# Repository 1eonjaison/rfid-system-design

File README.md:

# RFID System Design

This project is a custom PCB designed for a potential RFID-based key fob system.

The PCB incorporates a planar spiral coil, electronic components, switches and connections for a display. The project focuses on applying electronic circuit design and PCB layout principles.

---

## How It Works

The system is designed around a PCB spiral coil that may be used for inductive communication with RFID tags or key fobs.

The PCB design includes:

- **Spiral Coil** – A PCB-integrated coil intended for inductive signal transmission or reception.
- **Electronic Circuitry** – Components and connections for processing electrical signals.
- **Battery Holder** – Provides a connection for a coin-cell battery.
- **Switches** – Allow user interaction with the circuit.
- **Display Connections** – A footprint for connecting an LCD display.
- **Test Points** – Allow electrical measurements and circuit testing.

---

## PCB Design

The project involved:

- Designing the PCB layout.
- Placing electronic components and footprints.
- Routing electrical connections between components.
- Creating a planar spiral coil.
- Using copper layers and ground regions.
- Producing a physical PCB prototype.

---

## Project Evaluation

This project helped me develop my understanding of PCB design, component placement, circuit routing and electronic system development.

It also provided practical experience in translating a digital PCB layout into a manufactured circuit board.

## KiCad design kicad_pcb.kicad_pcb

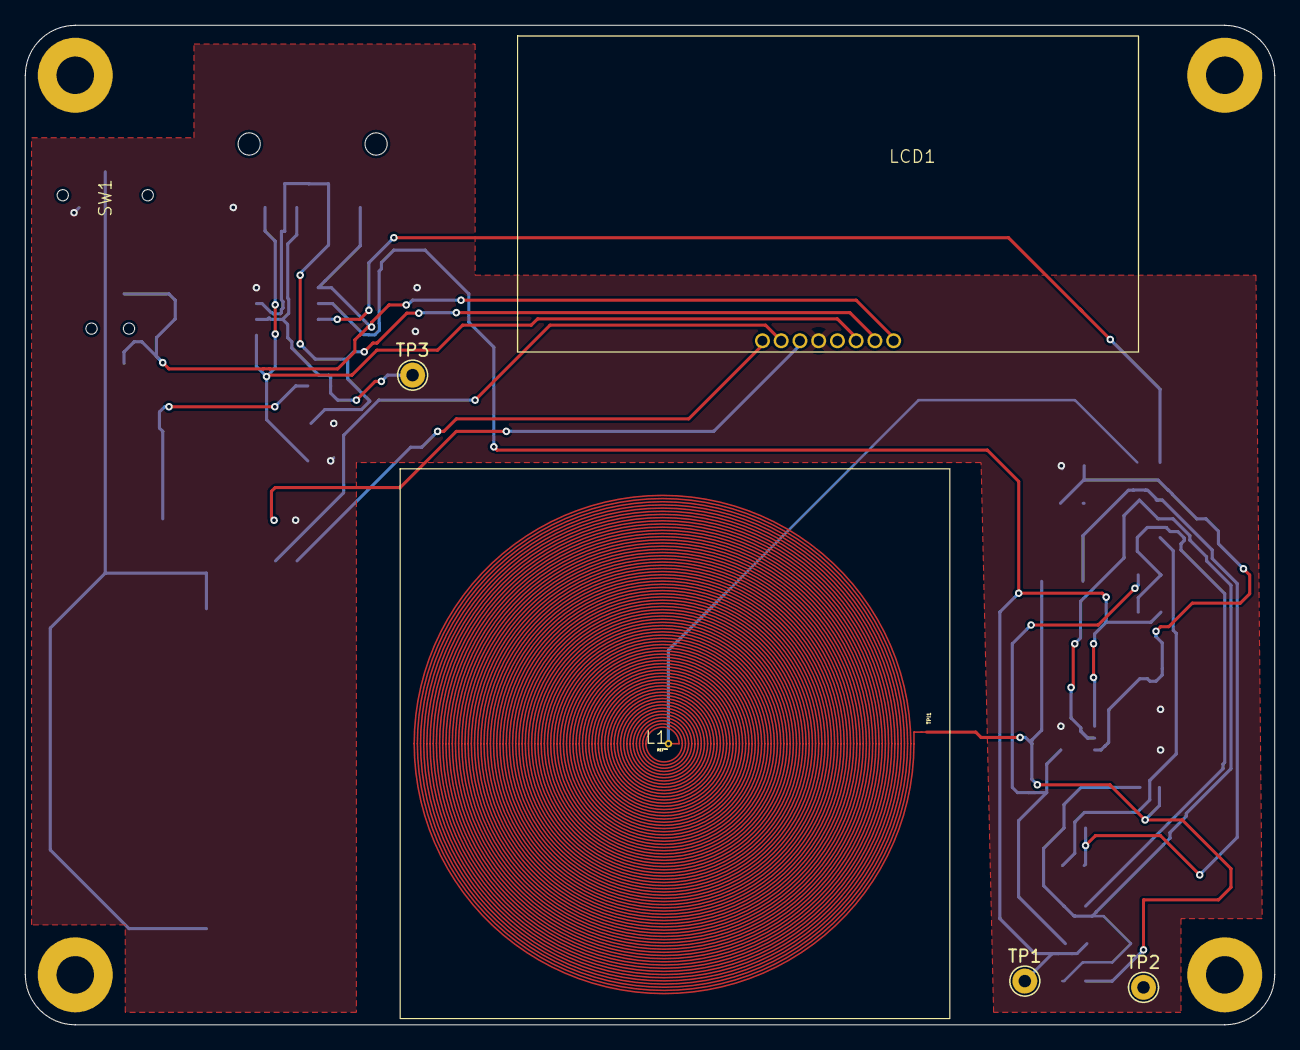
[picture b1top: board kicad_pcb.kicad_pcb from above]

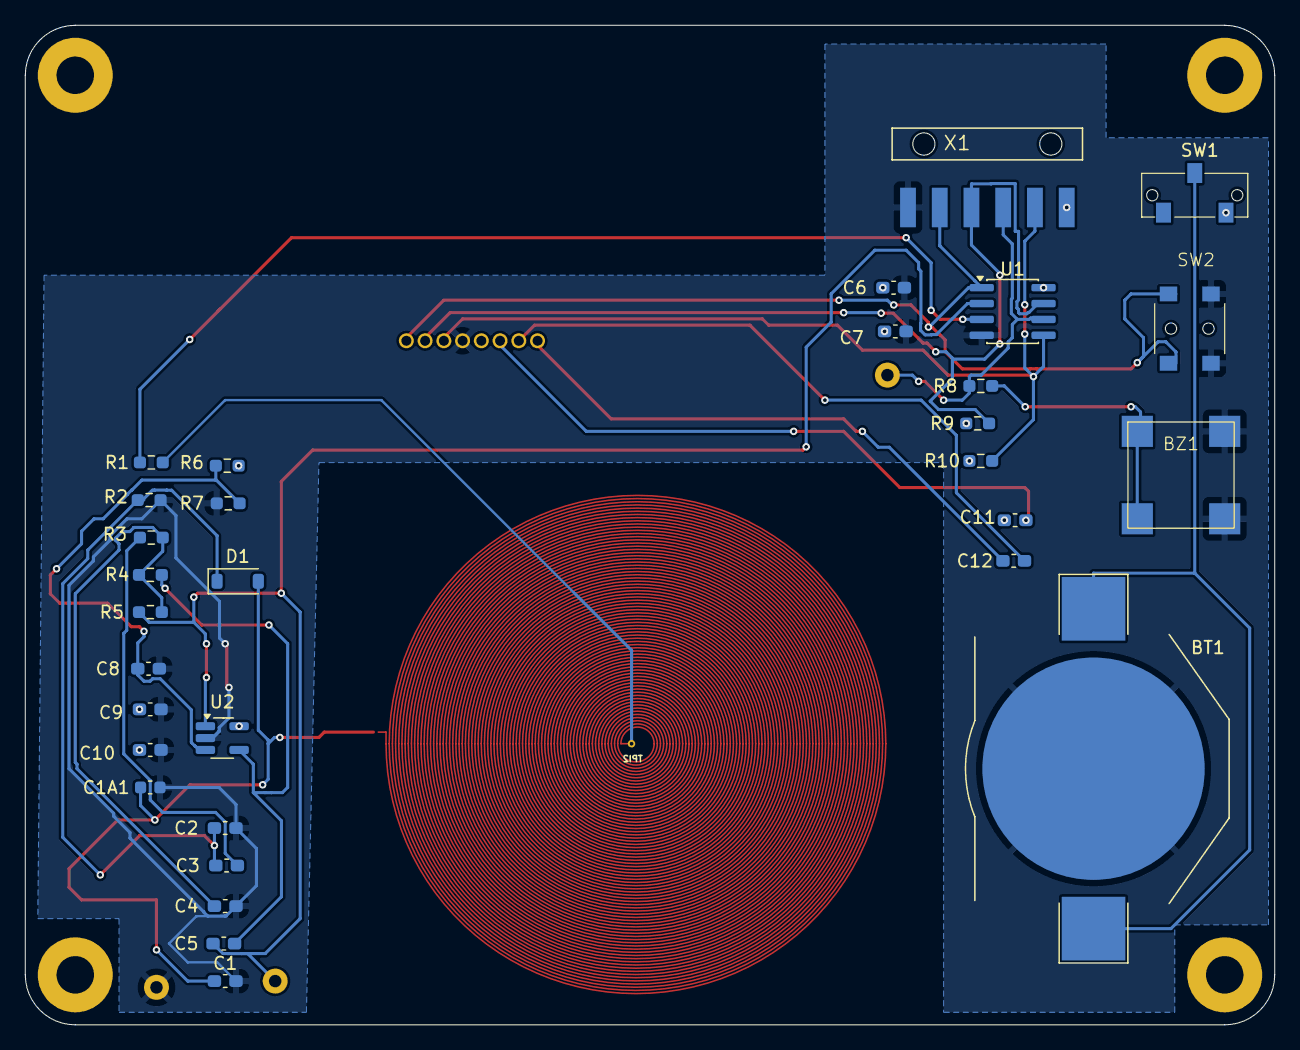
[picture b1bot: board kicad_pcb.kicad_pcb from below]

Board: 2 copper layers, 100.0 x 80.0 mm, 40 parts (31 on the bottom side), 19 nets.

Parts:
BT1: BatteryHolder_Keystone_3002_1x2032
BZ1: KSSGJ4D20
C1: 10nF; C_0603_1608Metric_Pad1.08x0.95mm_HandSolder
C1A1: C; C_0603_1608Metric
C2: 1nF; C_0603_1608Metric_Pad1.08x0.95mm_HandSolder
C3, C7, C8, C10: 100nF; C_0603_1608Metric_Pad1.08x0.95mm_HandSolder
C4: 4.7nF; C_0603_1608Metric_Pad1.08x0.95mm_HandSolder
C5: 10pF; C_0603_1608Metric_Pad1.08x0.95mm_HandSolder
C6, C9: 10uF; C_0603_1608Metric_Pad1.08x0.95mm_HandSolder
C11, C12: 1uF; C_0603_1608Metric_Pad1.08x0.95mm_HandSolder
D1: 1N4148W; D_SOD-123
H1, H2, H3, H4: MountingHole; MountingHole_3mm_Pad
L1: COIL
LCD1: NHD-C0216CiZ-FN-FBW-3V
R1: 100; R_0603_1608Metric_Pad0.98x0.95mm_HandSolder
R2: 470k; R_0603_1608Metric_Pad0.98x0.95mm_HandSolder
R3: 6.8k; R_0603_1608Metric_Pad0.98x0.95mm_HandSolder
R4: 47k; R_0603_1608Metric_Pad0.98x0.95mm_HandSolder
R5: 680k; R_0603_1608Metric_Pad0.98x0.95mm_HandSolder
R6, R7: 100k; R_0603_1608Metric_Pad0.98x0.95mm_HandSolder
R8: 1k; R_0603_1608Metric_Pad0.98x0.95mm_HandSolder
R9, R10: 4.7k; R_0603_1608Metric_Pad0.98x0.95mm_HandSolder
SW1: PowerSwitch
SW2: 1571262-1
TP1, TP2, TP3: TestPoint; TestPoint_THTPad_D2.0mm_Drill1.0mm
U1: ATtiny25-20SS; SOIC-8_3.9x4.9mm_P1.27mm
U2: SOT-23-5_HandSoldering
X1: MH06-1-SMD

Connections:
/BUZZER: R8.1, TP3.1, U1.6 (PB1), X1.3
/DEMOD: C5.1, R5.1, TP1.1, U1.2 (XTAL1/PB3), U2.1
/RFOUT: R1.1, U1.3 (XTAL2/PB4)
/RST: LCD1.1 (RST), SW2.1, U1.1 (~RESET/PB5), X1.5
/SCL: LCD1.2 (SCL), R9.2, U1.7 (PB2), X1.4
/SDA: LCD1.3 (SDA), R10.2, U1.5 (AREF/PB0), X1.2
GND: BT1.2, BZ1.2, C1.2, C1A1.2, C2.2, C4.2, C6.2, C7.2, C8.2, C9.2, C10.2, LCD1.4 (VSS), R2.2, R7.1, SW2.2, TP2.1, U1.4 (GND), U2.2 (V-), X1.6
unnamed: BT1.1, SW1.2
unnamed: BZ1.1, R8.2
unnamed: C3.2, R3.1
unnamed: C4.1, R3.2, R4.1, R5.2
unnamed: C1.1, C1A1.1, D1.2 (A)
unnamed: C2.1, C3.1, D1.1 (K), R2.1
unnamed: C12.2, LCD1.7 (C+)
unnamed: C12.1, LCD1.8 (C-)
unnamed: C11.2, LCD1.6 (VOUT)
unnamed: C5.2, R4.2, U2.4 (-)
VCC: C6.1, C7.1, C9.1, C10.1, C11.1, LCD1.5 (VDD), R6.2, R9.1, R10.1, SW1.3, U1.8 (VCC), U2.5 (V+), X1.1
VREF: C8.1, R6.1, R7.2, U2.3 (+)
